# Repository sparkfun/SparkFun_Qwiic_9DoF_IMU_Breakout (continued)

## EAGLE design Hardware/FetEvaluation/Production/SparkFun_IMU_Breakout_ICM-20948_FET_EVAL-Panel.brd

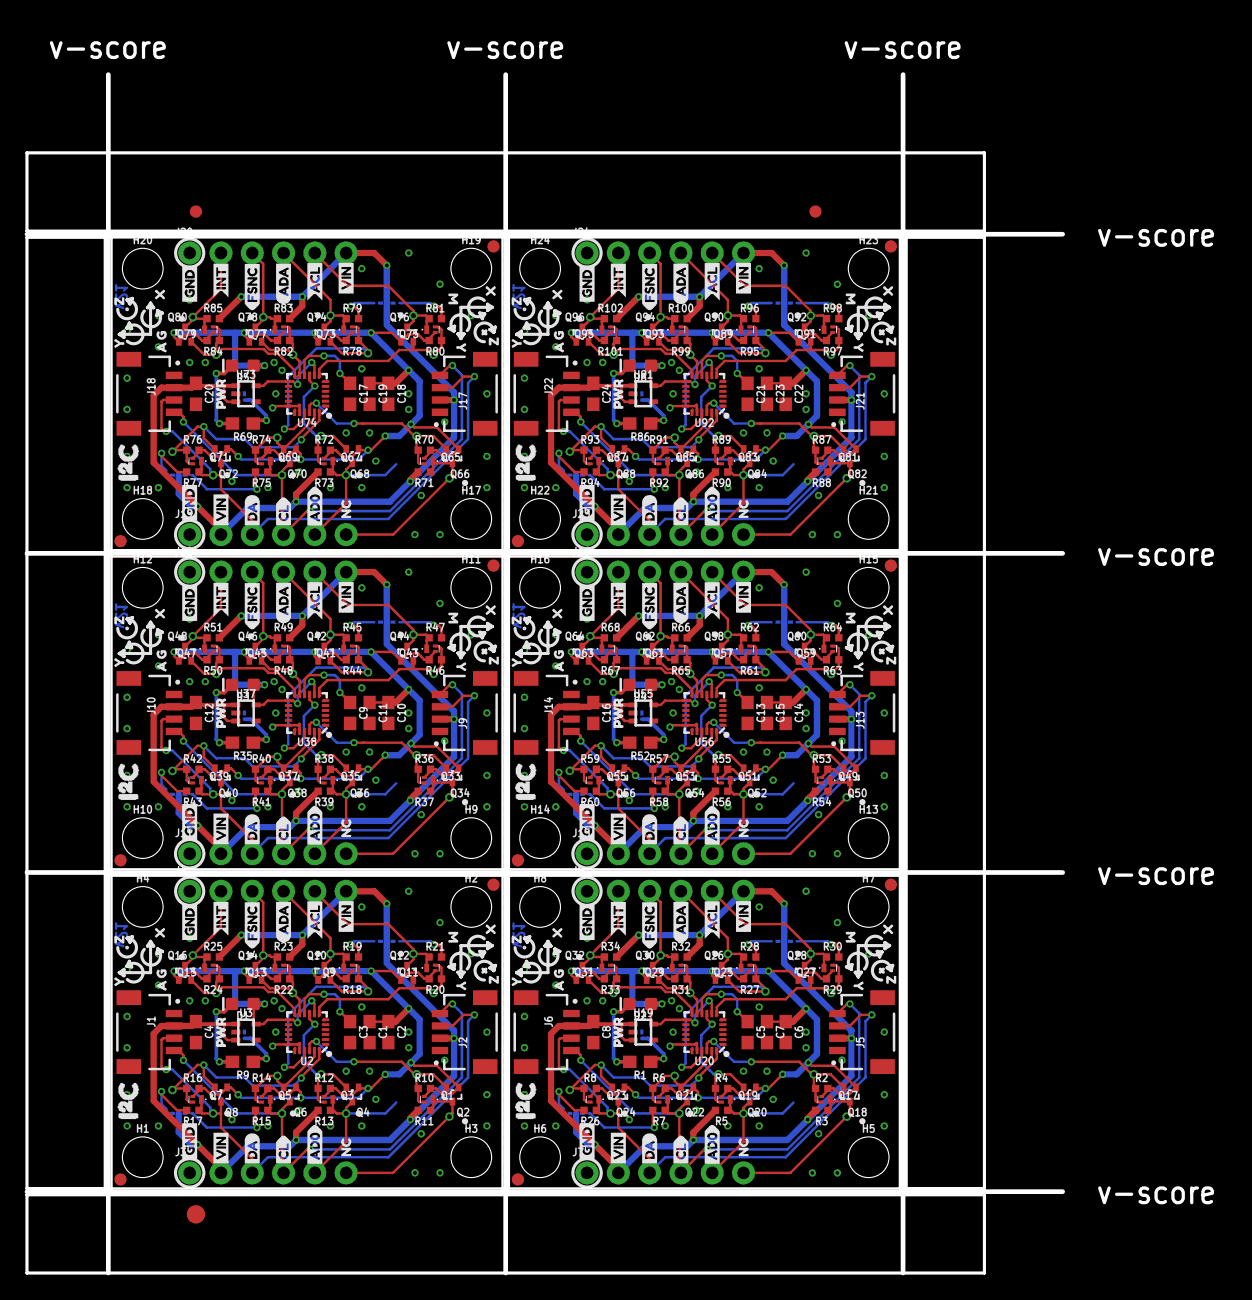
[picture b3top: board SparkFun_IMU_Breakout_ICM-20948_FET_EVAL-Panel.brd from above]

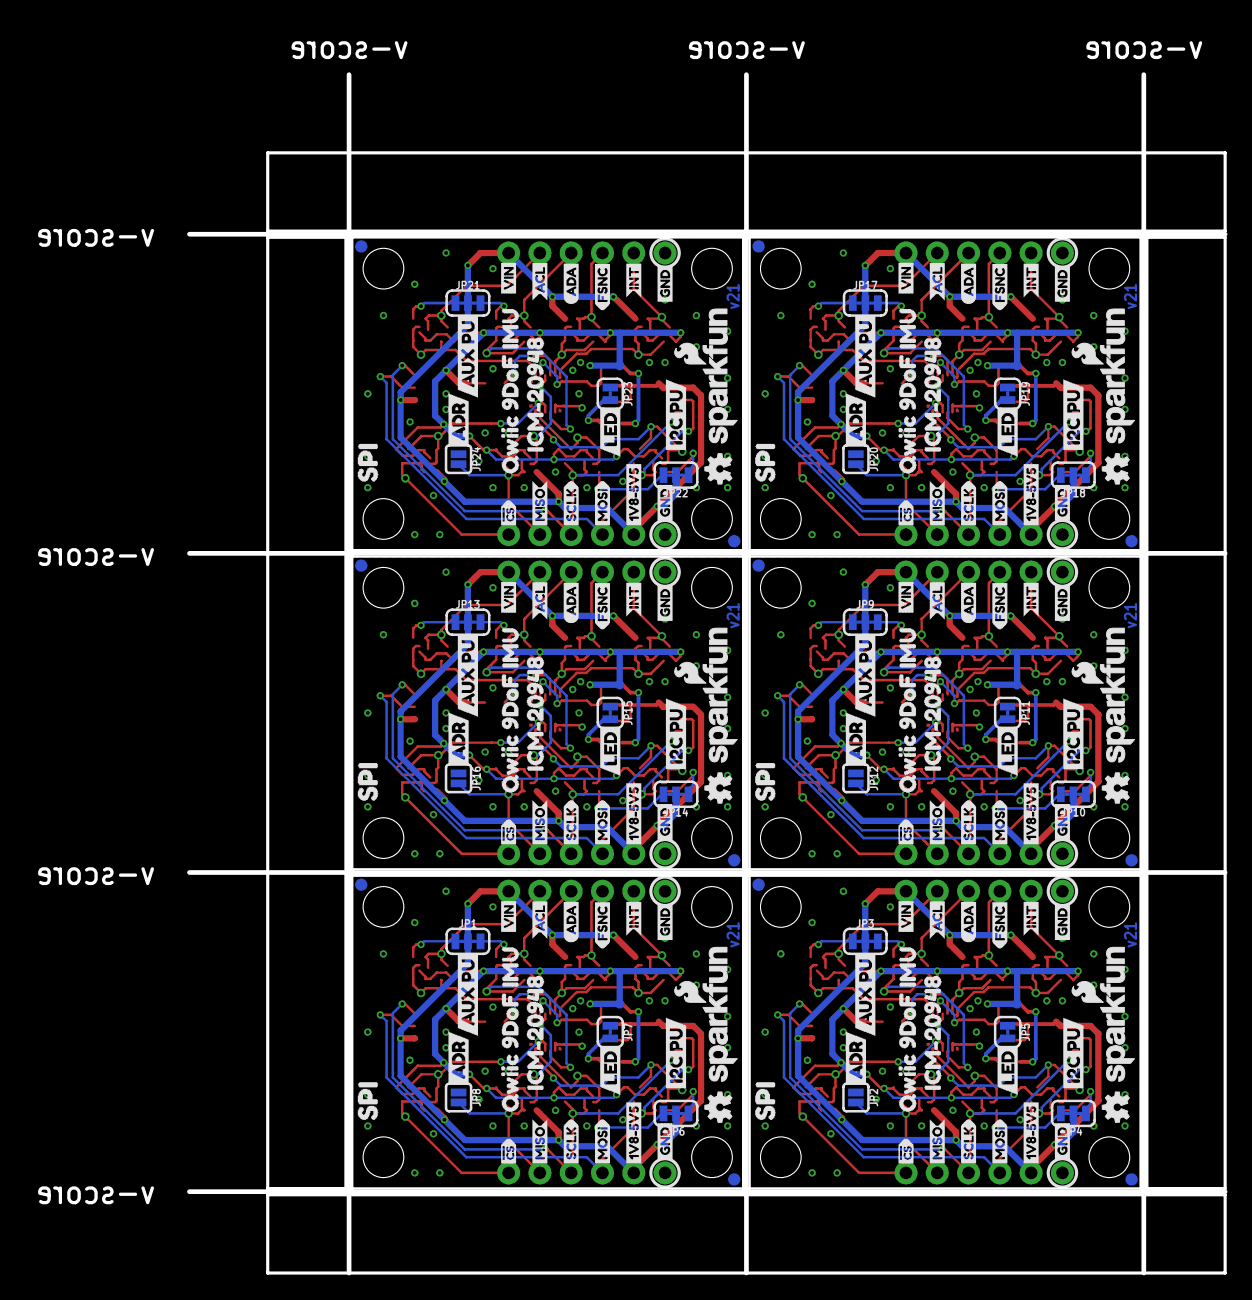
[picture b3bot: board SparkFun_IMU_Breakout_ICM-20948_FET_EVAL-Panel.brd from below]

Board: 2 copper layers, 84.1 x 97.3 mm, 705 parts (168 on the bottom side), 156 nets.

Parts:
C1, C4, C7, C8, C11, C12, C15, C16, C19, C20, C23, C24: 1.0uF; 0603
C2, C3, C5, C6, C9, C10, C13, C14, C17, C18, C21, C22: 0.1uF; 0603
D1, D2, D3, D4, D5, D6: RED; LED-0603
E$1, E$2: FIDUCIAL-1X2
E$3: FIDUCIAL-1.5X3
FD1, FD2, FD3, FD4, FD5, FD6, FD7, FD8, FD9, FD10, FD11, FD12, FD13, FD14, FD15, FD16, FD17, FD18, FD19, FD20, FD21, FD22, FD23, FD24: FIDUCIAL1X2; FIDUCIAL-1X2
H1, H2, H3, H4, H5, H6, H7, H8, H9, H10, H11, H12, H13, H14, H15, H16, H17, H18, H19, H20, H21, H22, H23, H24: STAND-OFF
J1, J2, J5, J6, J9, J10, J13, J14, J17, J18, J21, J22: JST04_1MM_RA
J3, J4, J7, J8, J11, J12, J15, J16, J19, J20, J23, J24: 1X06_NO_SILK
JP1, JP3, JP9, JP13, JP17, JP21: AUX; SMT-JUMPER_3_2-NC_TRACE_SILK
JP2, JP8, JP12, JP16, JP20, JP24: ADR; SMT-JUMPER_2_NO_SILK
JP4, JP6, JP10, JP14, JP18, JP22: I2C PU; SMT-JUMPER_3_2-NC_TRACE_SILK
JP5, JP7, JP11, JP15, JP19, JP23: LED; SMT-JUMPER_2_NC_TRACE_SILK
LOGO1, LOGO3, LOGO5, LOGO7, LOGO9, LOGO11: SFE_LOGO_NAME_FLAME.1_INCH; SFE_LOGO_NAME_FLAME_.1
LOGO2, LOGO4, LOGO6, LOGO8, LOGO10, LOGO12: OSHW-LOGOMINI; OSHW-LOGO-MINI
Q1, Q3, Q5, Q7, Q9, Q11, Q13, Q15, Q17, Q19, Q21, Q23, Q25, Q27, Q29, Q31, Q33, Q35, Q37, Q39, Q41, Q43, Q45, Q47, Q49, Q51, Q53, Q55, Q57, Q59, Q61, Q63, Q65, Q67, Q69, Q71, Q73, Q75, Q77, Q79, Q81, Q83, Q85, Q87, Q89, Q91, Q93, Q95: DMN2005LP4K-7; AP02001
Q2, Q4, Q6, Q8, Q10, Q12, Q14, Q16, Q18, Q20, Q22, Q24, Q26, Q28, Q30, Q32, Q34, Q36, Q38, Q40, Q42, Q44, Q46, Q48, Q50, Q52, Q54, Q56, Q58, Q60, Q62, Q64, Q66, Q68, Q70, Q72, Q74, Q76, Q78, Q80, Q82, Q84, Q86, Q88, Q90, Q92, Q94, Q96: RE1C002UN; SOT-416FL
R1, R9, R35, R52, R69, R86: 470; 0603
R2, R3, R4, R5, R6, R7, R8, R10, R11, R12, R13, R14, R15, R16, R17, R18, R19, R20, R21, R22, R23, R24, R25, R26, R27, R28, R29, R30, R31, R32, R33, R34, R36, R37, R38, R39, R40, R41, R42, R43, R44, R45, R46, R47, R48, R49, R50, R51, R53, R54, R55, R56, R57, R58, R59, R60, R61, R62, R63, R64, R65, R66, R67, R68, R70, R71, R72, R73, R74, R75, R76, R77, R78, R79, R80, R81, R82, R83, R84, R85, R87, R88, R89, R90, R91, R92, R93, R94, R95, R96, R97, R98, R99, R100, R101, R102: 2.2k; 0402-TIGHT
TP1, TP2, TP3, TP4, TP5, TP6: 1.8V; PAD.03X.03
U1, U4, U5, U6, U7, U8, U9, U10, U11, U12, U13, U14, U15, U16, U17, U18, U21, U22, U23, U24, U25, U26, U27, U28, U29, U30, U31, U32, U33, U34, U35, U36, U39, U40, U41, U42, U43, U44, U45, U46, U47, U48, U49, U50, U51, U52, U53, U54, U57, U58, U59, U60, U61, U62, U63, U64, U65, U66, U67, U68, U69, U70, U71, U72, U75, U76, U77, U78, U79, U80, U81, U82, U83, U84, U85, U86, U87, U88, U89, U90, U93, U94, U95, U96, U97, U98, U99, U100, U101, U102, U103, U104, U105, U106, U107, U108: TP; MINI_TEST_POINT
U2, U20, U38, U56, U74, U92: 9DoF IMU; QFN24-3X3
U3, U19, U37, U55, U73, U91: 1.8V/100mA; SC70
U$1, U$2, U$22, U$24, U$32, U$33, U$62, U$84, U$86, U$87, U$104, U$126, U$128, U$129, U$146, U$168, U$170, U$171, U$188, U$210, U$212, U$213, U$230, U$252: GND4
U$3, U$81, U$123, U$165, U$207, U$249: PWR0
U$4, U$21, U$46, U$61, U$88, U$103, U$130, U$145, U$172, U$187, U$214, U$229: INT3
U$5, U$20, U$47, U$60, U$89, U$102, U$131, U$144, U$173, U$186, U$215, U$228: FSNC2
U$6, U$19, U$48, U$59, U$90, U$101, U$132, U$143, U$174, U$185, U$216, U$227: ACL1
U$7, U$18, U$49, U$58, U$91, U$100, U$133, U$142, U$175, U$184, U$217, U$226: ADA0
U$8, U$50, U$92, U$134, U$176, U$218: MISO13
U$9, U$51, U$93, U$135, U$177, U$219: MOSI14
U$10, U$52, U$94, U$136, U$178, U$220: SCLK15
U$11, U$53, U$95, U$137, U$179, U$221: #CS16
U$12, U$54, U$96, U$138, U$180, U$222: 1V8#5V57
U$13, U$30, U$44, U$55, U$79, U$80, U$97, U$121, U$122, U$139, U$163, U$164, U$181, U$205, U$206, U$223, U$247, U$248: VIN5
U$14, U$56, U$98, U$140, U$182, U$224: NC17
U$15, U$77, U$119, U$161, U$203, U$245: CL4
U$16, U$78, U$120, U$162, U$204, U$246: DA2
U$17, U$57, U$99, U$141, U$183, U$225: AD012
U$23, U$83, U$125, U$167, U$209, U$251: ADR2
U$25, U$64, U$106, U$148, U$190, U$232: I2C_PU21
U$26, U$63, U$105, U$147, U$189, U$231: SPI19
U$27, U$65, U$107, U$149, U$191, U$233: AUX_PU24
U$28, U$31, U$85, U$127, U$169, U$211: ICM#2094820
U$29, U$66, U$108, U$150, U$192, U$234: LED23
U$34, U$40, U$67, U$73, U$109, U$115, U$151, U$157, U$193, U$199, U$235, U$241: X0
U$35, U$41, U$68, U$74, U$110, U$116, U$152, U$158, U$194, U$200, U$236, U$242: Y1
U$36, U$42, U$69, U$75, U$111, U$117, U$153, U$159, U$195, U$201, U$237, U$243: Z2
U$37, U$70, U$112, U$154, U$196, U$238: G5
U$38, U$71, U$113, U$155, U$197, U$239: A4
U$39, U$72, U$114, U$156, U$198, U$240: M3
U$43, U$76, U$118, U$160, U$202, U$244: QWIIC_9DOF_IMU_0
U$45, U$82, U$124, U$166, U$208, U$250: I#C1

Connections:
1.8V: C1.1, C2.1, D1.A, Q1.G, Q2.1, Q3.G, Q4.1, Q5.G, Q6.1, Q7.G, Q8.1, Q9.G, Q10.1, Q11.G, Q12.1, Q13.G, Q14.1, Q15.G, Q16.1, R10.2, R12.2, R14.2, R16.2, R18.2, R20.2, R22.2, R24.2, TP1.P$1, U2.8, U2.13, U3.5
1.8V1: C6.1, C7.1, D2.A, Q17.G, Q18.1, Q19.G, Q20.1, Q21.G, Q22.1, Q23.G, Q24.1, Q25.G, Q26.1, Q27.G, Q28.1, Q29.G, Q30.1, Q31.G, Q32.1, R2.2, R4.2, R6.2, R8.2, R27.2, R29.2, R31.2, R33.2, TP2.P$1, U19.5, U20.8, U20.13
1.8V2: C10.1, C11.1, D3.A, Q33.G, Q34.1, Q35.G, Q36.1, Q37.G, Q38.1, Q39.G, Q40.1, Q41.G, Q42.1, Q43.G, Q44.1, Q45.G, Q46.1, Q47.G, Q48.1, R36.2, R38.2, R40.2, R42.2, R44.2, R46.2, R48.2, R50.2, TP3.P$1, U37.5, U38.8, U38.13
1.8V3: C14.1, C15.1, D4.A, Q49.G, Q50.1, Q51.G, Q52.1, Q53.G, Q54.1, Q55.G, Q56.1, Q57.G, Q58.1, Q59.G, Q60.1, Q61.G, Q62.1, Q63.G, Q64.1, R53.2, R55.2, R57.2, R59.2, R61.2, R63.2, R65.2, R67.2, TP4.P$1, U55.5, U56.8, U56.13
1.8V4: C18.1, C19.1, D5.A, Q65.G, Q66.1, Q67.G, Q68.1, Q69.G, Q70.1, Q71.G, Q72.1, Q73.G, Q74.1, Q75.G, Q76.1, Q77.G, Q78.1, Q79.G, Q80.1, R70.2, R72.2, R74.2, R76.2, R78.2, R80.2, R82.2, R84.2, TP5.P$1, U73.5, U74.8, U74.13
1.8V5: C22.1, C23.1, D6.A, Q81.G, Q82.1, Q83.G, Q84.1, Q85.G, Q86.1, Q87.G, Q88.1, Q89.G, Q90.1, Q91.G, Q92.1, Q93.G, Q94.1, Q95.G, Q96.1, R87.2, R89.2, R91.2, R93.2, R95.2, R97.2, R99.2, R101.2, TP6.P$1, U91.5, U92.8, U92.13
!CS: Q1.S, Q2.2, R10.1, U2.22, U17.P$1
!CS1: Q17.S, Q18.2, R2.1, U20.22, U35.P$1
!CS2: Q33.S, Q34.2, R36.1, U38.22, U53.P$1
!CS3: Q49.S, Q50.2, R53.1, U56.22, U71.P$1
!CS4: Q65.S, Q66.2, R70.1, U74.22, U89.P$1
!CS5: Q81.S, Q82.2, R87.1, U92.22, U107.P$1
!CS!_VIN: J3.6, Q1.D, Q2.3, R11.1, U18.P$1
!CS!_VIN1: J7.6, Q17.D, Q18.3, R3.1, U36.P$1
!CS!_VIN2: J11.6, Q33.D, Q34.3, R37.1, U54.P$1
!CS!_VIN3: J15.6, Q49.D, Q50.3, R54.1, U72.P$1
!CS!_VIN4: J19.6, Q65.D, Q66.3, R71.1, U90.P$1
!CS!_VIN5: J23.6, Q81.D, Q82.3, R88.1, U108.P$1
AD0/SDO: Q3.S, Q4.2, R12.1, U2.9, U15.P$1
AD0/SDO1: Q19.S, Q20.2, R4.1, U20.9, U33.P$1
AD0/SDO2: Q35.S, Q36.2, R38.1, U38.9, U51.P$1
AD0/SDO3: Q51.S, Q52.2, R55.1, U56.9, U69.P$1
AD0/SDO4: Q67.S, Q68.2, R72.1, U74.9, U87.P$1
AD0/SDO5: Q83.S, Q84.2, R89.1, U92.9, U105.P$1
AD0/SDO_VIN: J3.5, JP2.2, Q3.D, Q4.3, R13.1, U16.P$1
AD0/SDO_VIN1: J7.5, JP8.2, Q19.D, Q20.3, R5.1, U34.P$1
AD0/SDO_VIN2: J11.5, JP12.2, Q35.D, Q36.3, R39.1, U52.P$1
AD0/SDO_VIN3: J15.5, JP16.2, Q51.D, Q52.3, R56.1, U70.P$1
AD0/SDO_VIN4: J19.5, JP20.2, Q67.D, Q68.3, R73.1, U88.P$1
AD0/SDO_VIN5: J23.5, JP24.2, Q83.D, Q84.3, R90.1, U106.P$1
AUX_CL: Q11.S, Q12.2, R20.1, U2.7, U5.P$1
AUX_CL1: Q27.S, Q28.2, R29.1, U20.7, U23.P$1
AUX_CL2: Q43.S, Q44.2, R46.1, U38.7, U41.P$1
AUX_CL3: Q59.S, Q60.2, R63.1, U56.7, U59.P$1
AUX_CL4: Q75.S, Q76.2, R80.1, U74.7, U77.P$1
AUX_CL5: Q91.S, Q92.2, R97.1, U92.7, U95.P$1
AUX_CL_VIN: J4.5, Q11.D, Q12.3, R21.1, U6.P$1
AUX_CL_VIN1: J8.5, Q27.D, Q28.3, R30.1, U24.P$1
AUX_CL_VIN2: J12.5, Q43.D, Q44.3, R47.1, U42.P$1
AUX_CL_VIN3: J16.5, Q59.D, Q60.3, R64.1, U60.P$1
AUX_CL_VIN4: J20.5, Q75.D, Q76.3, R81.1, U78.P$1
AUX_CL_VIN5: J24.5, Q91.D, Q92.3, R98.1, U96.P$1
AUX_CL_VIN_JMP: JP3.1, R21.2
AUX_CL_VIN_JMP1: JP1.1, R30.2
AUX_CL_VIN_JMP2: JP9.1, R47.2
AUX_CL_VIN_JMP3: JP13.1, R64.2
AUX_CL_VIN_JMP4: JP17.1, R81.2
AUX_CL_VIN_JMP5: JP21.1, R98.2
AUX_DA: Q9.S, Q10.2, R18.1, U1.P$1, U2.21
AUX_DA1: Q25.S, Q26.2, R27.1, U20.21, U21.P$1
AUX_DA2: Q41.S, Q42.2, R44.1, U38.21, U39.P$1
AUX_DA3: Q57.S, Q58.2, R61.1, U56.21, U57.P$1
AUX_DA4: Q73.S, Q74.2, R78.1, U74.21, U75.P$1
AUX_DA5: Q89.S, Q90.2, R95.1, U92.21, U93.P$1
AUX_DA_VIN: J4.4, Q9.D, Q10.3, R19.1, U4.P$1
AUX_DA_VIN1: J8.4, Q25.D, Q26.3, R28.1, U22.P$1
AUX_DA_VIN2: J12.4, Q41.D, Q42.3, R45.1, U40.P$1
AUX_DA_VIN3: J16.4, Q57.D, Q58.3, R62.1, U58.P$1
AUX_DA_VIN4: J20.4, Q73.D, Q74.3, R79.1, U76.P$1
AUX_DA_VIN5: J24.4, Q89.D, Q90.3, R96.1, U94.P$1
AUX_DA_VIN_JMP: JP3.3, R19.2
AUX_DA_VIN_JMP1: JP1.3, R28.2
AUX_DA_VIN_JMP2: JP9.3, R45.2
AUX_DA_VIN_JMP3: JP13.3, R62.2
AUX_DA_VIN_JMP4: JP17.3, R79.2
AUX_DA_VIN_JMP5: JP21.3, R96.2
FSYNC: Q13.S, Q14.2, R22.1, U2.11, U8.P$1
FSYNC1: Q29.S, Q30.2, R31.1, U20.11, U26.P$1
FSYNC2: Q45.S, Q46.2, R48.1, U38.11, U44.P$1
FSYNC3: Q61.S, Q62.2, R65.1, U56.11, U62.P$1
FSYNC4: Q77.S, Q78.2, R82.1, U74.11, U80.P$1
FSYNC5: Q93.S, Q94.2, R99.1, U92.11, U98.P$1
FSYNC_VIN: J4.3, Q13.D, Q14.3, R23.1, U7.P$1
FSYNC_VIN1: J8.3, Q29.D, Q30.3, R32.1, U25.P$1
FSYNC_VIN2: J12.3, Q45.D, Q46.3, R49.1, U43.P$1
FSYNC_VIN3: J16.3, Q61.D, Q62.3, R66.1, U61.P$1
FSYNC_VIN4: J20.3, Q77.D, Q78.3, R83.1, U79.P$1
FSYNC_VIN5: J24.3, Q93.D, Q94.3, R100.1, U97.P$1
GND: C1.2, C2.2, C3.2, C4.2, J1.1, J2.1, J3.1, J4.1, JP2.1, JP5.1, U2.18, U2.20, U3.2
GND1: C5.2, C6.2, C7.2, C8.2, J5.1, J6.1, J7.1, J8.1, JP7.1, JP8.1, U19.2, U20.18, U20.20
GND2: C9.2, C10.2, C11.2, C12.2, J9.1, J10.1, J11.1, J12.1, JP11.1, JP12.1, U37.2, U38.18, U38.20
GND3: C13.2, C14.2, C15.2, C16.2, J13.1, J14.1, J15.1, J16.1, JP15.1, JP16.1, U55.2, U56.18, U56.20
GND4: C17.2, C18.2, C19.2, C20.2, J17.1, J18.1, J19.1, J20.1, JP19.1, JP20.1, U73.2, U74.18, U74.20
GND5: C21.2, C22.2, C23.2, C24.2, J21.1, J22.1, J23.1, J24.1, JP23.1, JP24.1, U91.2, U92.18, U92.20
INT: Q15.S, Q16.2, R24.1, U2.12, U9.P$1
INT1: Q31.S, Q32.2, R33.1, U20.12, U27.P$1
INT2: Q47.S, Q48.2, R50.1, U38.12, U45.P$1
INT3: Q63.S, Q64.2, R67.1, U56.12, U63.P$1
INT4: Q79.S, Q80.2, R84.1, U74.12, U81.P$1
INT5: Q95.S, Q96.2, R101.1, U92.12, U99.P$1
INT_VIN: J4.2, Q15.D, Q16.3, R25.1, U10.P$1
INT_VIN1: J8.2, Q31.D, Q32.3, R34.1, U28.P$1
INT_VIN2: J12.2, Q47.D, Q48.3, R51.1, U46.P$1
INT_VIN3: J16.2, Q63.D, Q64.3, R68.1, U64.P$1
INT_VIN4: J20.2, Q79.D, Q80.3, R85.1, U82.P$1
INT_VIN5: J24.2, Q95.D, Q96.3, R102.1, U100.P$1
unnamed: C3.1, U2.10
unnamed: C5.1, U20.10
unnamed: D2.C, R1.2
unnamed: JP7.2, R1.1
unnamed: C9.1, U38.10
unnamed: D3.C, R35.2
unnamed: JP11.2, R35.1
unnamed: D1.C, R9.2
unnamed: JP5.2, R9.1
unnamed: C13.1, U56.10
unnamed: D4.C, R52.2
unnamed: JP15.2, R52.1
unnamed: C17.1, U74.10
unnamed: D5.C, R69.2
unnamed: JP19.2, R69.1
unnamed: C21.1, U92.10
unnamed: D6.C, R86.2
unnamed: JP23.2, R86.1
SCL/SCLK: Q5.S, Q6.2, R14.1, U2.23, U13.P$1
SCL/SCLK1: Q21.S, Q22.2, R6.1, U20.23, U31.P$1
SCL/SCLK2: Q37.S, Q38.2, R40.1, U38.23, U49.P$1
SCL/SCLK3: Q53.S, Q54.2, R57.1, U56.23, U67.P$1
SCL/SCLK4: Q69.S, Q70.2, R74.1, U74.23, U85.P$1
SCL/SCLK5: Q85.S, Q86.2, R91.1, U92.23, U103.P$1
SCL/SCLK_VIN: J1.4, J2.4, J3.4, Q5.D, Q6.3, R15.1, U14.P$1
SCL/SCLK_VIN1: J5.4, J6.4, J7.4, Q21.D, Q22.3, R7.1, U32.P$1
SCL/SCLK_VIN2: J9.4, J10.4, J11.4, Q37.D, Q38.3, R41.1, U50.P$1
SCL/SCLK_VIN3: J13.4, J14.4, J15.4, Q53.D, Q54.3, R58.1, U68.P$1
SCL/SCLK_VIN4: J17.4, J18.4, J19.4, Q69.D, Q70.3, R75.1, U86.P$1
SCL/SCLK_VIN5: J21.4, J22.4, J23.4, Q85.D, Q86.3, R92.1, U104.P$1
SCL/SCLK_VIN_JMP: JP4.3, R15.2
SCL/SCLK_VIN_JMP1: JP6.3, R7.2
SCL/SCLK_VIN_JMP2: JP10.3, R41.2
SCL/SCLK_VIN_JMP3: JP14.3, R58.2
SCL/SCLK_VIN_JMP4: JP18.3, R75.2
SCL/SCLK_VIN_JMP5: JP22.3, R92.2
SDA/SDI: Q7.S, Q8.2, R16.1, U2.24, U11.P$1
SDA/SDI1: Q23.S, Q24.2, R8.1, U20.24, U29.P$1
SDA/SDI2: Q39.S, Q40.2, R42.1, U38.24, U47.P$1
SDA/SDI3: Q55.S, Q56.2, R59.1, U56.24, U65.P$1
SDA/SDI4: Q71.S, Q72.2, R76.1, U74.24, U83.P$1
SDA/SDI5: Q87.S, Q88.2, R93.1, U92.24, U101.P$1
SDA/SDI_VIN: J1.3, J2.3, J3.3, Q7.D, Q8.3, R17.1, U12.P$1
SDA/SDI_VIN1: J5.3, J6.3, J7.3, Q23.D, Q24.3, R26.1, U30.P$1
SDA/SDI_VIN2: J9.3, J10.3, J11.3, Q39.D, Q40.3, R43.1, U48.P$1
SDA/SDI_VIN3: J13.3, J14.3, J15.3, Q55.D, Q56.3, R60.1, U66.P$1
SDA/SDI_VIN4: J17.3, J18.3, J19.3, Q71.D, Q72.3, R77.1, U84.P$1
SDA/SDI_VIN5: J21.3, J22.3, J23.3, Q87.D, Q88.3, R94.1, U102.P$1
SDA/SDI_VIN_JMP: JP4.1, R17.2
SDA/SDI_VIN_JMP1: JP6.1, R26.2
SDA/SDI_VIN_JMP2: JP10.1, R43.2
SDA/SDI_VIN_JMP3: JP14.1, R60.2
SDA/SDI_VIN_JMP4: JP18.1, R77.2
SDA/SDI_VIN_JMP5: JP22.1, R94.2
VIN: C4.1, J1.2, J2.2, J3.2, J4.6, JP3.2, JP4.2, R11.2, R13.2, R23.2, R25.2, U3.1, U3.3
VIN1: C8.1, J5.2, J6.2, J7.2, J8.6, JP1.2, JP6.2, R3.2, R5.2, R32.2, R34.2, U19.1, U19.3
VIN2: C12.1, J9.2, J10.2, J11.2, J12.6, JP9.2, JP10.2, R37.2, R39.2, R49.2, R51.2, U37.1, U37.3
VIN3: C16.1, J13.2, J14.2, J15.2, J16.6, JP13.2, JP14.2, R54.2, R56.2, R66.2, R68.2, U55.1, U55.3
VIN4: C20.1, J17.2, J18.2, J19.2, J20.6, JP17.2, JP18.2, R71.2, R73.2, R83.2, R85.2, U73.1, U73.3
VIN5: C24.1, J21.2, J22.2, J23.2, J24.6, JP21.2, JP22.2, R88.2, R90.2, R100.2, R102.2, U91.1, U91.3

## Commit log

2019-01-15 Create schematic and initial board layout
2019-01-15 Prettified the schematic
2019-01-16 Push to work from laptop
2019-01-16 95% ready for review commit
2019-01-16 Design review
    Made all routing look as clean as possible
2019-01-16 Trace routing changes during design review
2019-01-16 Fixes notes from issue #1
    In response to issue #1 I have:
    - Replaced an existing 0.1 uF cap with 1.0 uF
    - Changed address references to hex in .sch
    - Questioned why we worry about vector font now that we use Buzzard
    - Tried LED at 1.8V w and w/o CL resistor (1k). All is well
    - Fixed all silk issues
2019-01-17 Add PWR LED and axes labels
2019-01-17 Reposition axis labels
2019-01-18 Fixed items 1-7 of issue #2
    1. Added PCB to BOM, and built in a reminder to the BOM ULP to do the same
    2. Changed the name to "SparkFun 9DoF IMU Breakout - ICM-20948 (Qwiic)" and now the silk name reads "Qwiic 9DoF IMU /n ICM-20948"
    3. Will not flip the board after approving DRC errors
    4. Fixed
    5. Fixed
    6. Done
2019-01-18 Fixed I2C heasder order
    Also adjusted silkcreen labels to reflect the new order
2019-01-18 Approved all errors
2019-01-18 Revert "Approved all errors"
    This reverts commit c58a3cda532a6d6b9316c1cbf57724f808b0484f.
2019-01-18 Well, I meant to say that I approved all *approvable* errors...
2019-01-29 Add Invensense Motion Processor SW docu
2019-03-08 Add documentation
2019-03-08 Swap TXB0108 for TXS0108 - still needs last check, design review, and finalization
2019-03-11 v20
    v20 is intended to fix the I2C communications. We've identified that the TXB0108 logic level translation IC was unable to drive open-drain busses. To address this we've replaced that IC with the TXS0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
2019-03-14 Post design review changes for v20
    - PWR silk changed to text only
    - Moved P1 indicator on ICM-20948
    - I<sup>2<\sup>C
    - AD0 -> ADR
    - No more '0' label for ADR
    - Vin range double checked
2019-03-14 Final checklist review with Eric v20
2019-03-14 Reove checklists
2019-04-11 Fix I2C Pullup Issue
    The combination of pullup resistors on the breakout, within the TXS0108, and on the BlackBoard Qwiic Level shifter conspired to make it impossible for the ICM to pull the data line low.
    Fix is to rely on only the internal pullup resistors within the TXS0108.
    Also removed a stray silk item from the board
2019-04-11 Made assembly sheet nicer
2019-04-15 Cleanup
    Empty directories
2019-04-19 Laid out board for MOSFET trick evaluation (prototype)
2019-04-19 Updated test point package with keepout
2019-04-19 Commit for design review
2019-04-23 Move CC block, ready for proto review
2019-04-23 Changes from design review
2019-04-23 Better pour
2019-05-09 Laid out v30
2019-05-09 Ran board design checklist ahead of the review
2019-05-09 Changes from design review
    Level shifter circuit spacing
    Axes indicators
    Routing touch-ups
    LED resistor change
2019-05-09 Remove redundant values on MOSFETs
2019-05-09 Fix spacing on MOSFET level shifter
2019-05-20 Fix short circuit
2019-05-28 Remove FET Eval schematic and board
2019-05-28 Remove cheklists
2019-06-03 Fix swapped silk for v31
    Silk was mislabeled after changing the order of the "secondary" side headers.
2019-06-04 Triple-check changes w/ Eli
    Increased axes label readability, made routing out of mosfets uniform (very small copper changes)
2019-06-04 ??? Eagle Changes ???
    Only ran the DRC
2020-10-20 added python package link to readme
2026-05-07 Docs port to GH Pages
    Initial commit for porting docs for this from internal host (Learn) to GH Pages.
2026-05-07 GH Pages Workflow
    Adding GH Pages workflow file
2026-05-07 Update Introduction.md
    Fixing image link error
2026-05-07 Update Introduction.md
    Testing to see if image is actually causing the build error
2026-05-07 Update docusaurus.config.ts
    Fixing baseurl typo
